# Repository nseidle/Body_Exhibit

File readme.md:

WOW Museum Body Exhibit
==============

The body exhibit allows children to press one of twelve buttons and see that part of the skeletal or organ system light up. An audio track saying the organ/bone name in English and Spanish is heard. An information audio track is heard if the button is pressed a second time. 

The system monitors the state of 12 buttons. When a button is pressed a string of 8 LEDs is lit and plays the corresponding MP3 track. I designed a custom shield to allow for JST connections to each channel (LED+button). 

Materials used:

* [SparkFun Mega2560](https://www.sparkfun.com/products/11007)
* A whole bunch of [Arcade Buttons](https://www.sparkfun.com/products/9336)
* [SparkFun MP3 Shield](https://www.sparkfun.com/products/12660)
* [MicroSD Card](https://www.sparkfun.com/products/11609) (Any size up to 64GB behemoths should do)
* [SparkFun Audio Amplifier](https://www.sparkfun.com/products/11044)
* [10k Trimpot for volume](https://www.sparkfun.com/products/9806)
* [Couple 10k resistors](https://www.sparkfun.com/products/11508)
* [SparkFun MegaShield Kit](https://www.sparkfun.com/products/9346) (used just the headers to connect to custom shield)
* [5V Wall Adapter](https://www.sparkfun.com/products/12889)
* [DC Barrel Jack](https://www.sparkfun.com/products/119)
* [Waterproof Speakers](http://www.amazon.com/gp/product/B001ES8X9M) because you need speakers that can mount flat on a wall and not be damaged by small, poking fingers

The custom shield uses a bunch of passives:
* 12 x [2N3904 NPN Transistors](https://www.sparkfun.com/products/521)
* 12 x [4-pin jumper connectors](https://www.sparkfun.com/products/9916)
* 12 x [10k Ohm resistors](https://www.sparkfun.com/products/11508) are optional. I used the internal pullups instead.
* 12 x [330 Ohm resistors](https://www.sparkfun.com/products/11507)
* 12 x [47 Ohm resistors](https://www.sparkfun.com/products/10969) from resistor kit
* [String of white LEDs](http://www.amazon.com/gp/product/B00P7OMKD4) cut into lengths of 10 LEDs
* Lots of [ribbon wire](https://www.sparkfun.com/products/10647)

I experimented with some of the cheap amplifiers found on Amazon. The SparkFun class-D amplifier was louder and a lot more clean than the TDA42934 based stereo amplifiers. The original shield design had a space for the TDA42934 amplifier but I'm going to change that on the next version.

The string of LEDs is the type that has three thin wires and a blob of epoxy over a 1206 sized SMD LED. The wire is enamelized so you have to burn the enamel off before you can solder to it. I use a blob of solder on the end of my iron and hold it there for 5-10 seconds to burn the enamel off. You should probably do so in a well ventilated because it smells pretty rough.

To prep the audio amp for external control: cut the small jumper, solder in two 10k PTH resistors, and then the 10k trim pot. This will allow user controllable volume. It is *very* loud and *very* clean with a good speaker and a wall power supply. Powering the MP3 player and audio amp via USB will introduce buzzing; I used an external 5V wall supply to power the amp directly.

The SparkFun Mega connects to the MP3 Shield via SPI pins and a handful of control pins. This was a bit of a hassle because the Mega has SPI pins in a weird place. In the future I will probably wire the ISP header from the Mega to the 2x6 pin SPI/ISP connector on the shield.

The MP3 shield "-" and "R" pins are wired to the "-" and "+" pins of the "In" port of the audio amp. The out pins of the audio amp are connected to the speaker. The audio amp's S or shutdown pin is connected to A1 so that we can shut it down when not playing an MP3.

The Mega2560 has a bug in its bootloader that doesn't allow normal usage of the watchdog. Because this is an exhibit that can be left on for weeks at a time I needed a method to prevent system hangs. I found a good solution [here](http://forum.arduino.cc/index.php?topic=62813.25) - thanks draythomp!

Another lesson: Label all the wires, sometimes in multiple places. When the wiring gets rough the labels are what will keep you sane. 

License Information
-------------------
The **code** is beerware; if you see me (or any other SparkFun employee) at the local, and you've found our code helpful, please buy us a round!

Please use, reuse, and modify these files as you see fit. Please maintain attribution to SparkFun Electronics and release anything derivative under the same license.

Distributed as-is; no warranty is given.

- Your friends at SparkFun.

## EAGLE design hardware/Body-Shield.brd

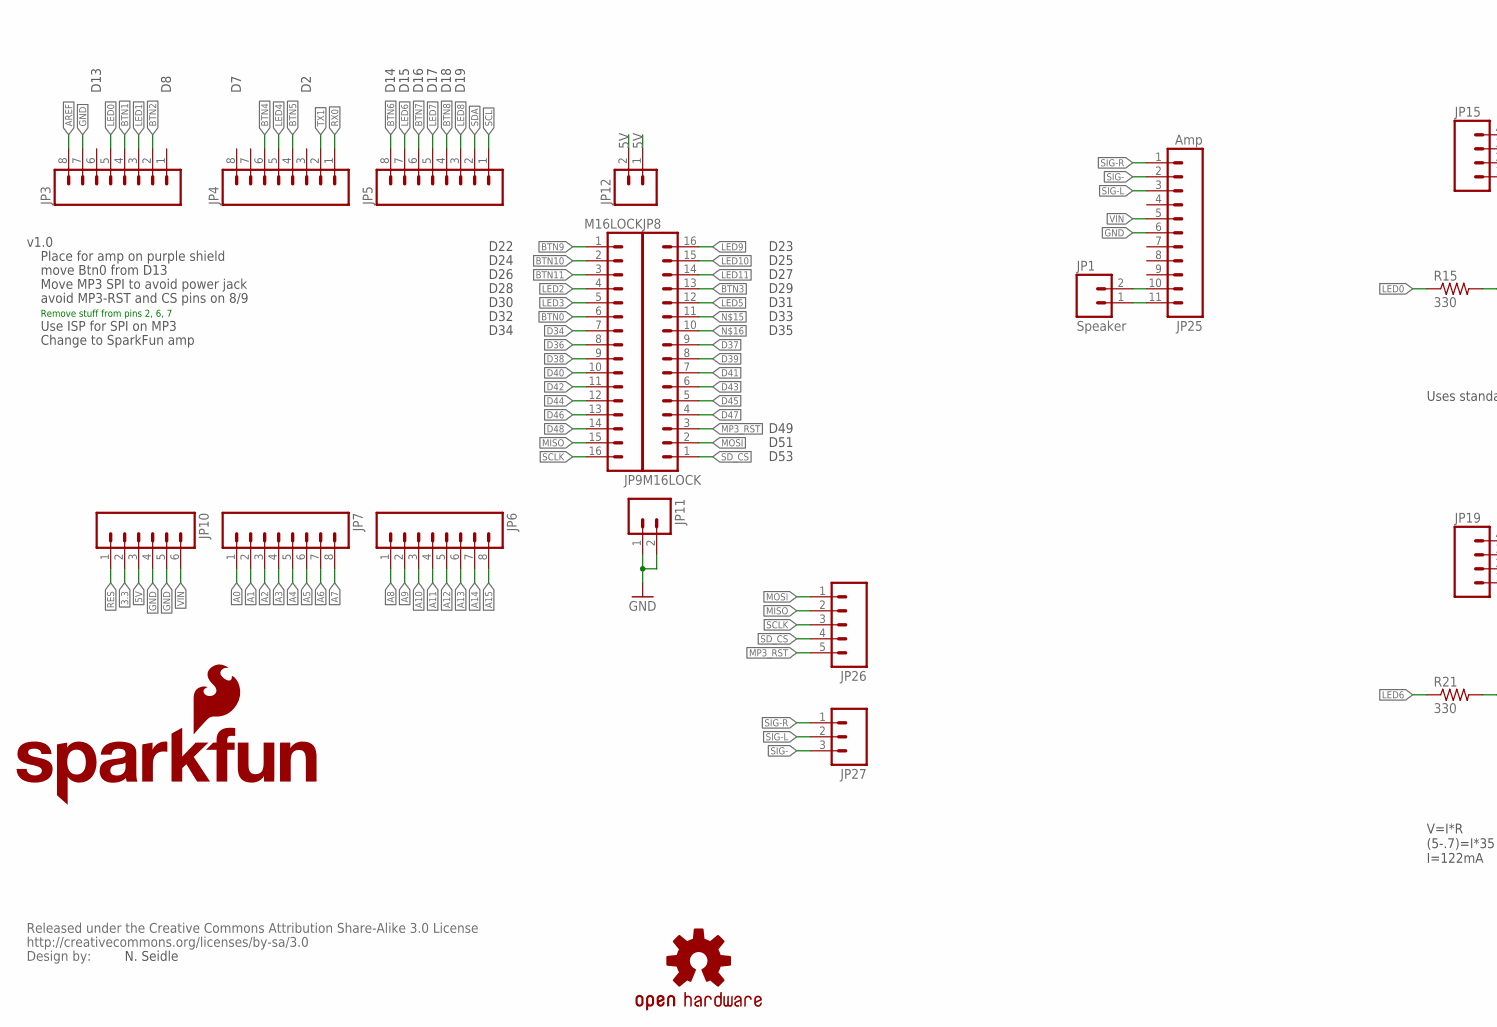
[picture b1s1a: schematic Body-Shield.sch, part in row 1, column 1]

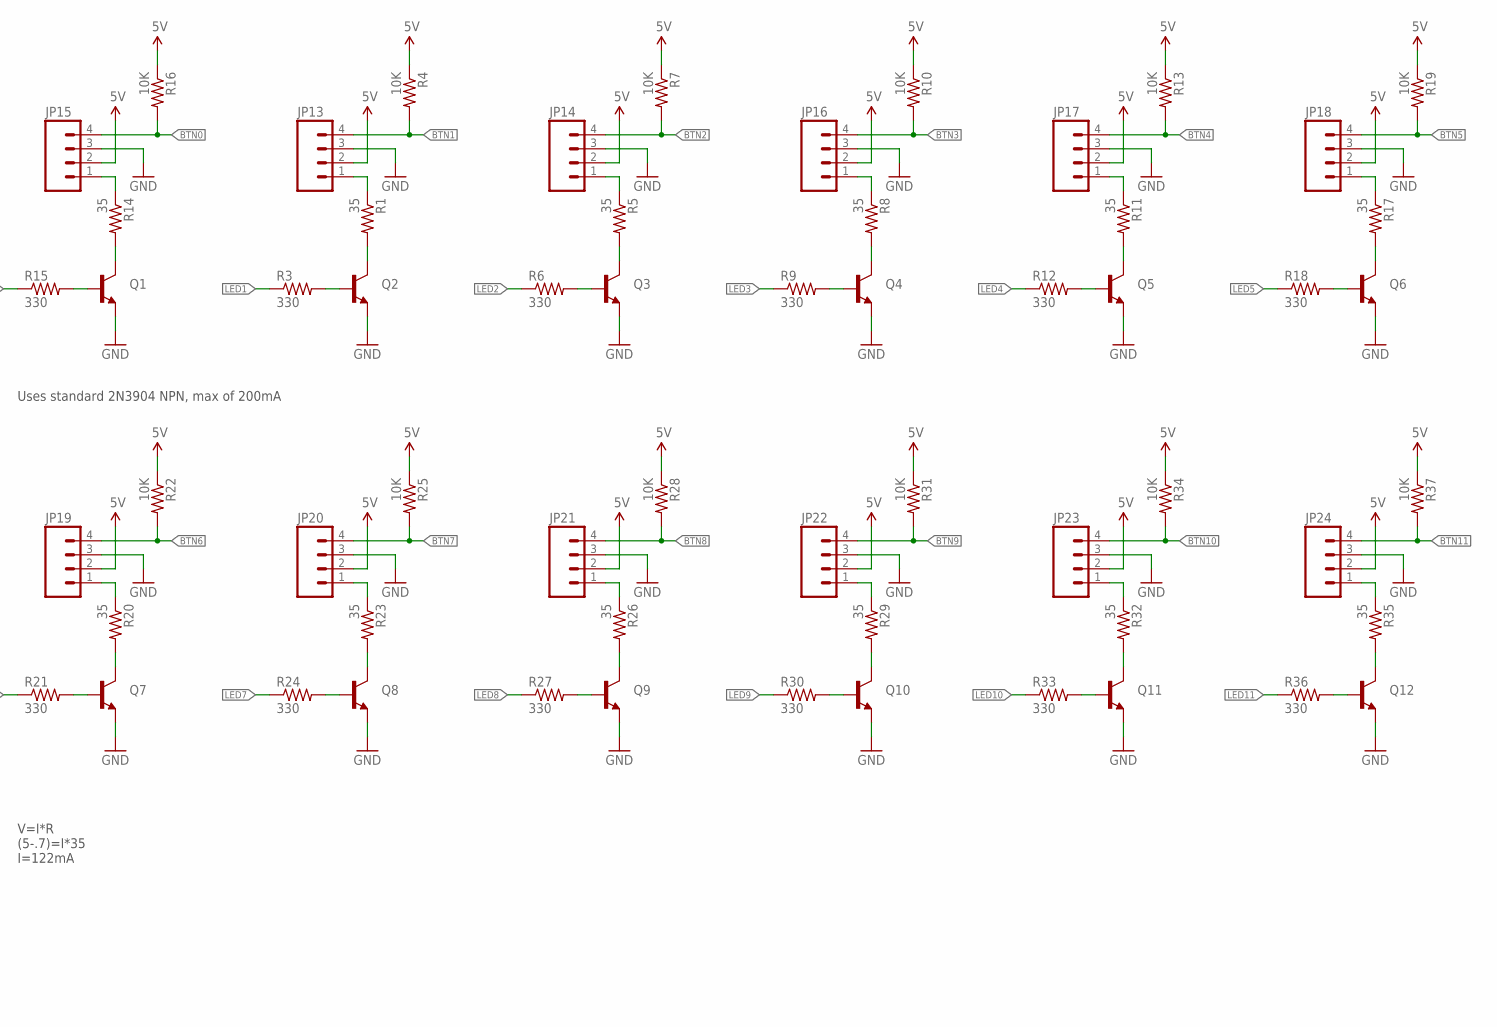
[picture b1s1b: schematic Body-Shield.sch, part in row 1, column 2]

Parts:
JP1: Speaker; JST-2-PTH-VERT
JP3, JP4, JP5, JP6, JP7: M08LOCK; 1X08_LOCK
JP8, JP9: M16LOCK; 1X16_LOCK
JP10: M06LOCK; 1X06_LOCK
JP11, JP12: M02LOCK; 1X02_LOCK
JP13, JP14, JP15, JP16, JP17, JP18, JP19, JP20, JP21, JP22, JP23, JP24: M04JST-PTH-VERT; JST-4-PTH-VERT
JP25: Amp; 1X11
JP26: M05JST; JST-5-PTH
JP27: M03JST-PTH; JST-3-PTH
LOGO1: SFE_LOGO_NAME_FLAME.1_INCH; SFE_LOGO_NAME_FLAME_.1
LOGO2: OSHW-LOGOS; OSHW-LOGO-S
Q1, Q2, Q3, Q4, Q5, Q6, Q7, Q8, Q9, Q10, Q11, Q12: TRANSISTOR_NPN2N3904; TO-92
R1, R5, R8, R11, R14, R17, R20, R23, R26, R29, R32, R35: 35; AXIAL-0.3
R3, R6, R9, R12, R15, R18, R21, R24, R27, R30, R33, R36: 330; AXIAL-0.3
R4, R7, R10, R13, R16, R19, R22, R25, R28, R31, R34, R37: 10K; AXIAL-0.3
U$2: CREATIVE_COMMONS

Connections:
3.3: JP10.2
5V: JP10.3, JP12.1, JP12.2, JP13.2, JP14.2, JP15.2, JP16.2, JP17.2, JP18.2, JP19.2, JP20.2, JP21.2, JP22.2, JP23.2, JP24.2, R4.P$1 (1), R7.P$1 (1), R10.P$1 (1), R13.P$1 (1), R16.P$1 (1), R19.P$1 (1), R22.P$1 (1), R25.P$1 (1), R28.P$1 (1), R31.P$1 (1), R34.P$1 (1), R37.P$1 (1)
A0: JP7.1
A1: JP7.2
A2: JP7.3
A3: JP7.4
A4: JP7.5
A5: JP7.6
A6: JP7.7
A7: JP7.8
A8: JP6.1
A9: JP6.2
A10: JP6.3
A11: JP6.4
A12: JP6.5
A13: JP6.6
A14: JP6.7
A15: JP6.8
AREF: JP3.8
BTN0: JP9.6, JP15.4, R16.P$2 (2)
BTN1: JP3.4, JP13.4, R4.P$2 (2)
BTN2: JP3.2, JP14.4, R7.P$2 (2)
BTN3: JP8.13, JP16.4, R10.P$2 (2)
BTN4: JP4.6, JP17.4, R13.P$2 (2)
BTN5: JP4.4, JP18.4, R19.P$2 (2)
BTN6: JP5.8, JP19.4, R22.P$2 (2)
BTN7: JP5.6, JP20.4, R25.P$2 (2)
BTN8: JP5.4, JP21.4, R28.P$2 (2)
BTN9: JP9.1, JP22.4, R31.P$2 (2)
BTN10: JP9.2, JP23.4, R34.P$2 (2)
BTN11: JP9.3, JP24.4, R37.P$2 (2)
D34: JP9.7
D36: JP9.8
D37: JP8.9
D38: JP9.9
D39: JP8.8
D40: JP9.10
D41: JP8.7
D42: JP9.11
D43: JP8.6
D44: JP9.12
D45: JP8.5
D46: JP9.13
D47: JP8.4
D48: JP9.14
GND: JP3.7, JP10.4, JP10.5, JP11.1, JP11.2, JP13.3, JP14.3, JP15.3, JP16.3, JP17.3, JP18.3, JP19.3, JP20.3, JP21.3, JP22.3, JP23.3, JP24.3, JP25.6, Q1.1 (E), Q2.1 (E), Q3.1 (E), Q4.1 (E), Q5.1 (E), Q6.1 (E), Q7.1 (E), Q8.1 (E), Q9.1 (E), Q10.1 (E), Q11.1 (E), Q12.1 (E)
LED0: JP3.5, R15.P$1 (1)
LED1: JP3.3, R3.P$1 (1)
LED2: JP9.4, R6.P$1 (1)
LED3: JP9.5, R9.P$1 (1)
LED4: JP4.5, R12.P$1 (1)
LED5: JP8.12, R18.P$1 (1)
LED6: JP5.7, R21.P$1 (1)
LED7: JP5.5, R24.P$1 (1)
LED8: JP5.3, R27.P$1 (1)
LED9: JP8.16, R30.P$1 (1)
LED10: JP8.15, R33.P$1 (1)
LED11: JP8.14, R36.P$1 (1)
MISO: JP9.15, JP26.2
MOSI: JP8.2, JP26.1
MP3_RST: JP8.3, JP26.5
unnamed: JP13.1, R1.P$1 (1)
unnamed: Q2.3 (C), R1.P$2 (2)
unnamed: Q2.2 (B), R3.P$2 (2)
unnamed: JP14.1, R5.P$1 (1)
unnamed: Q3.3 (C), R5.P$2 (2)
unnamed: Q3.2 (B), R6.P$2 (2)
unnamed: JP16.1, R8.P$1 (1)
unnamed: JP15.1, R14.P$1 (1)
unnamed: Q1.3 (C), R14.P$2 (2)
unnamed: Q1.2 (B), R15.P$2 (2)
unnamed: Q4.3 (C), R8.P$2 (2)
unnamed: Q4.2 (B), R9.P$2 (2)
unnamed: JP17.1, R11.P$1 (1)
unnamed: Q5.3 (C), R11.P$2 (2)
unnamed: Q5.2 (B), R12.P$2 (2)
unnamed: JP18.1, R17.P$1 (1)
unnamed: Q6.3 (C), R17.P$2 (2)
unnamed: Q6.2 (B), R18.P$2 (2)
unnamed: JP19.1, R20.P$1 (1)
unnamed: Q7.3 (C), R20.P$2 (2)
unnamed: Q7.2 (B), R21.P$2 (2)
unnamed: JP20.1, R23.P$1 (1)
unnamed: Q8.3 (C), R23.P$2 (2)
unnamed: Q8.2 (B), R24.P$2 (2)
unnamed: JP21.1, R26.P$1 (1)
unnamed: Q9.3 (C), R26.P$2 (2)
unnamed: Q9.2 (B), R27.P$2 (2)
unnamed: JP22.1, R29.P$1 (1)
unnamed: Q10.3 (C), R29.P$2 (2)
unnamed: Q10.2 (B), R30.P$2 (2)
unnamed: JP23.1, R32.P$1 (1)
unnamed: Q11.3 (C), R32.P$2 (2)
unnamed: Q11.2 (B), R33.P$2 (2)
unnamed: JP24.1, R35.P$1 (1)
unnamed: Q12.3 (C), R35.P$2 (2)
unnamed: Q12.2 (B), R36.P$2 (2)
unnamed: JP1.1, JP25.11
unnamed: JP1.2, JP25.10
RES: JP10.1
RX0: JP4.1
SCL: JP5.1
SCLK: JP9.16, JP26.3
SDA: JP5.2
SD_CS: JP8.1, JP26.4
SIG-: JP25.2, JP27.3
SIG-L: JP25.3, JP27.2
SIG-R: JP25.1, JP27.1
TX1: JP4.2
VIN: JP10.6, JP25.5

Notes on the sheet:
N. Seidle
Place for amp on purple shield
v1.0
V=I*R (5-.7)=I*35 I=122mA
D22
D24
D26
D28
D30
D32
D34
D23
D25
D27
D29
D31
D33
D35
D14
D15
D16
D17
D18
D19
D49
D51
D53
D13
move Btn0 from D13
Move MP3 SPI to avoid power jack
avoid MP3-RST and CS pins on 8/9
Remove stuff from pins 2, 6, 7
Uses standard 2N3904 NPN, max of 200mA
Use ISP for SPI on MP3
Change to SparkFun amp

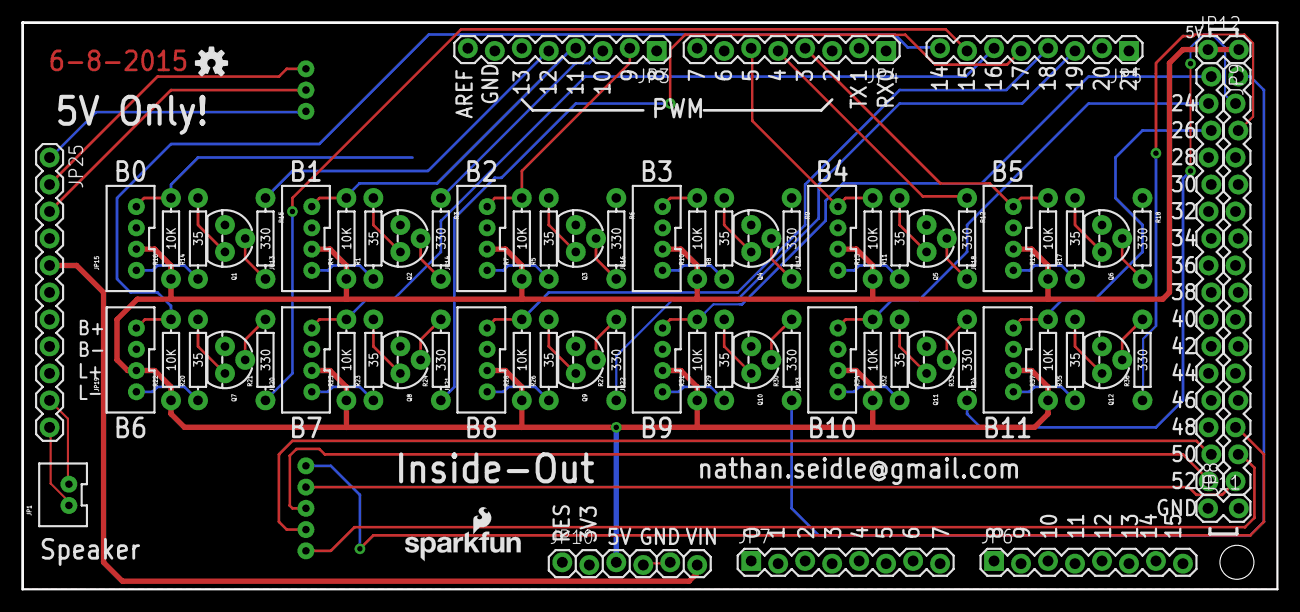
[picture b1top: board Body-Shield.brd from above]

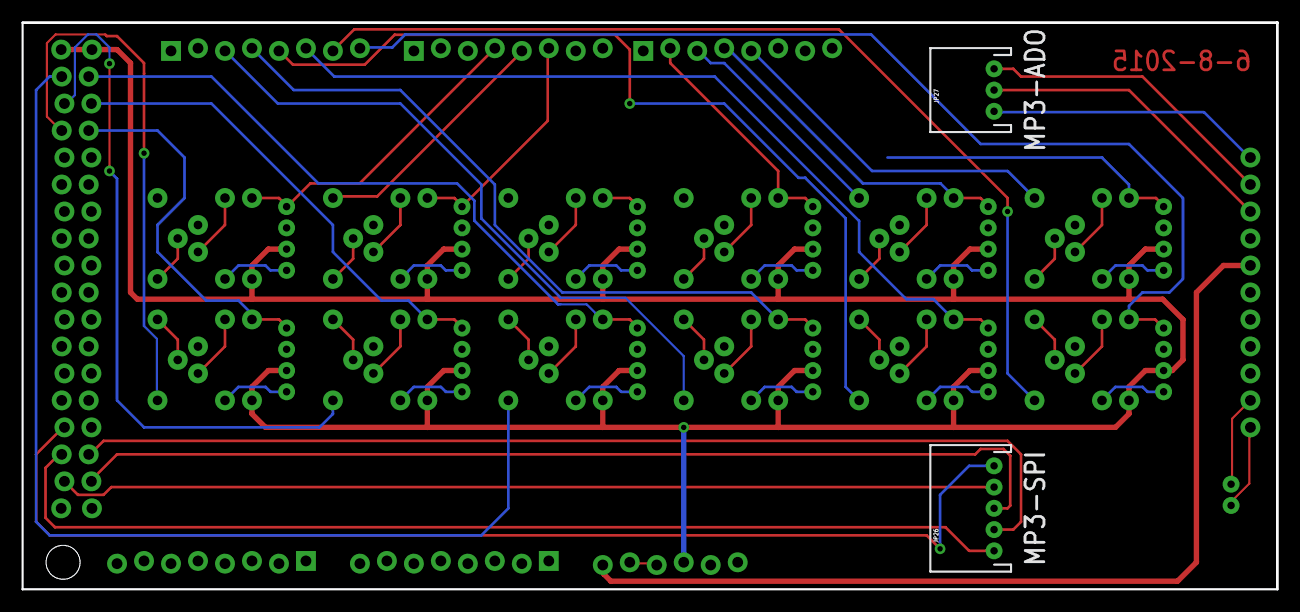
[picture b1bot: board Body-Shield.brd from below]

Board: 2 copper layers, 118.1 x 53.3 mm, 77 parts (2 on the bottom side), 73 nets.

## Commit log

2015-06-09 :octocat: Added .gitattributes & .gitignore files
2015-06-09 Initial commit
    What was sent to OSHPark
2015-10-26 Adding firmware, sound files, etc
2015-10-26 Update readme with images
2015-10-26 Adding description of the mechanical stackup

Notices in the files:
parts and their libraries:
SparkFun: Released under the Creative Commons Attribution Share-Alike 3.0 License
SparkFun: http://creativecommons.org/licenses/by-sa/3.0
SparkFun-Connectors: Licensing: CC v3.0 Share-Alike You are welcome to use this library for commercial purposes.
